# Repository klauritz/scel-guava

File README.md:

# Smart Campus Energy Lab - Team Guava
Current Members: Sawinna Huang, Kenneth Lauritzen, Rammell Transfiguracion

*** 
Welcome to Team Guava's repo!

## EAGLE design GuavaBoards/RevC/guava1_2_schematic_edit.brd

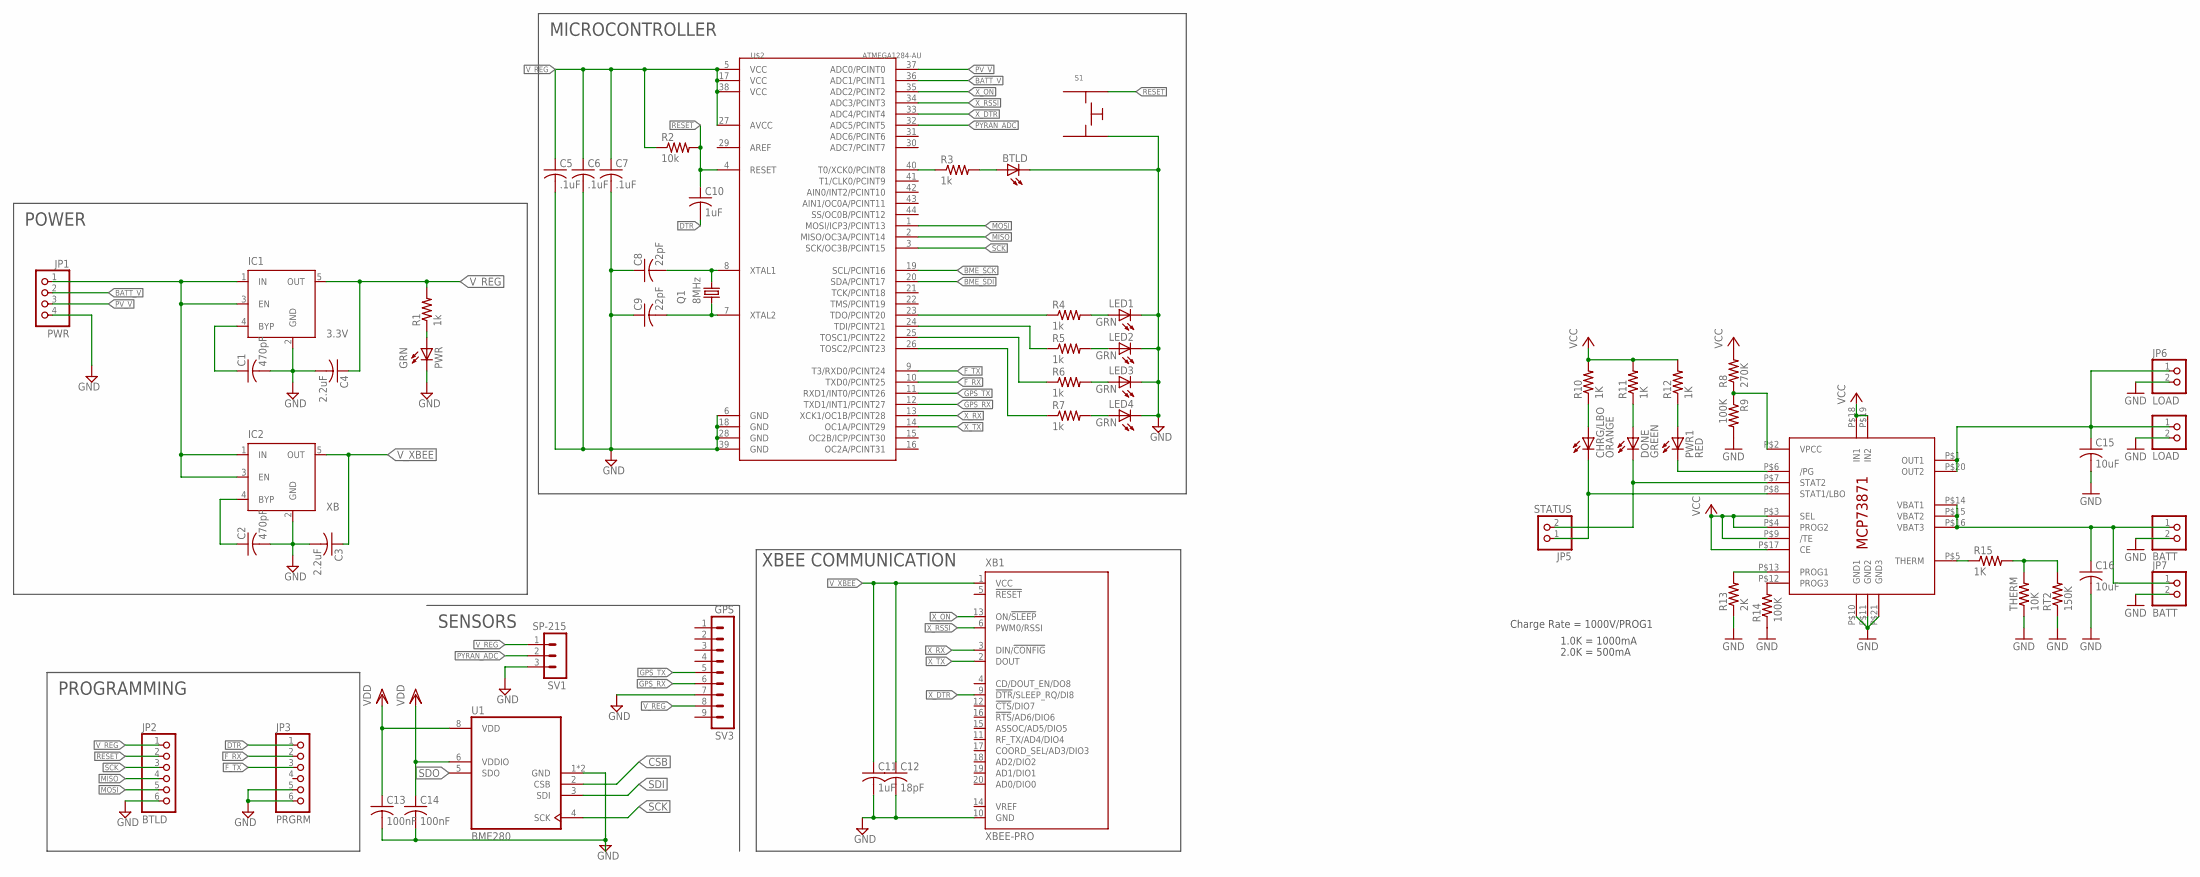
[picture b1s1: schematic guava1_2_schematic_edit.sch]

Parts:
BATT: JST_2PIN-SMT-RA; JST-PH-2-SMT-RA
BTLD: LEDCHIPLED_0805; CHIPLED_0805
C1, C2: 470pF; C0402
C3, C4: 2.2uF; C0603
C5, C6, C7: .1uF; C0603
C8, C9: 22pF; C0402
C10, C11: 1uF; C0805
C12: 18pF; C0805
C13, C14: 100nF; C025-024X044
C15, C16: 10uF; C0805K
CHRG/LBO: ORANGE; CHIP-LED0805
DONE: GREEN; CHIP-LED0805
IC1: 3.3V; SOT23-5
IC2: XB; SOT23-5
IC3: MCP73871; QFN20_4MM
JP1: PWR; 1X04
JP2: BTLD; 1X06
JP3: PRGRM; 1X06
JP5: STATUS; 1X02_OVAL
JP6: LOAD; 1X02_OVAL
JP7: BATT; 1X02_OVAL
LED1, LED2, LED3, LED4: GRN; CHIPLED_0805
LOAD: JST_2PIN-SMT-RA; JST-PH-2-SMT-RA
PWR: GRN; CHIPLED_0805
PWR1: RED; CHIP-LED0805
Q1: 8MHz; HC49UP
R1, R3, R4, R5, R6, R7: 1k; R0603
R2: 10k; R0603
R8: 270K; R0805
R9, R14: 100K; R0805
R10, R11, R12: 1K; R0805
R13: 2K; 0805-THM
R15: 1K; M0805
RT2: 150K; M0805
S1: PUSH_BUTTON_SPSTSMD; COM-12993
SV1: SP-215; MA03-1
SV3: GPS; MA09-1
THERM: 10K; 0805-THM
U1: BME280; PSON65P250X250X100-8N
U$2: ATMEGA1284-AU; 44A
XB1: XBEE-PRO

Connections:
BATT: BATT.1 (2), C16.1, IC3.P$14 (VBAT1), IC3.P$15 (VBAT2), IC3.P$16 (VBAT3), JP7.1
BATT_V: JP1.2, U$2.36 (ADC1/PCINT1)
BME_SCK: U$2.19 (SCL/PCINT16)
BME_SDI: U$2.20 (SDA/PCINT17)
CSB: C13.2, C14.2, U1.1 (GND), U1.2 (CSB), U1.7 (GND)
DTR: C10.2, JP3.1
F_RX: JP3.2, U$2.10 (TXD0/PCINT25)
F_TX: JP3.3, U$2.9 (T3/RXD0/PCINT24)
GND: BATT.2 (1), BTLD.C, C1.2, C2.2, C3.2, C4.2, C5.2, C6.2, C7.2, C8.1, C9.1, C11.2, C12.2, C15.2, C16.2, IC1.2 (GND), IC2.2 (GND), IC3.P$10 (GND1), IC3.P$11 (GND2), IC3.P$21 (GND3), JP1.4, JP2.6, JP3.5, JP3.6, JP6.2, JP7.2, LED1.C, LED2.C, LED3.C, LED4.C, LOAD.2 (1), PWR.C, R9.2, R13.1, R14.1, RT2.1, S1.3, SV1.3, SV3.7, THERM.1, U$2.6 (GND), U$2.18 (GND), U$2.28 (GND), U$2.39 (GND), XB1.10 (GND)
GPS_RX: SV3.6, U$2.12 (TXD1/INT1/PCINT27)
GPS_TX: SV3.5, U$2.11 (RXD1/INT0/PCINT26)
LED1: R4.1, U$2.23 (TDO/PCINT20)
LED2: R5.1, U$2.24 (TDI/PCINT21)
LED3: R6.1, U$2.25 (TOSC1/PCINT22)
LED4: R7.1, U$2.26 (TOSC2/PCINT23)
MISO: JP2.4, U$2.2 (MISO/OC3A/PCINT14)
MOSI: JP2.5, U$2.1 (MOSI/ICP3/PCINT13)
unnamed: C8.2, Q1.2, U$2.8 (XTAL1)
unnamed: C9.2, Q1.1, U$2.7 (XTAL2)
unnamed: BTLD.A, R3.2
unnamed: R3.1, U$2.40 (T0/XCK0/PCINT8)
unnamed: IC3.P$2 (VPCC), R8.1, R9.1
unnamed: C1.1, IC1.4 (BYP)
unnamed: PWR.A, R1.1
unnamed: LED4.A, R7.2
unnamed: LED2.A, R5.2
unnamed: LED3.A, R6.2
unnamed: LED1.A, R4.2
unnamed: IC3.P$6 (/PG), PWR1.C
unnamed: DONE.C, IC3.P$7 (STAT2), JP5.2
unnamed: C2.1, IC2.4 (BYP)
unnamed: CHRG/LBO.C, IC3.P$8 (STAT1/LBO), JP5.1
unnamed: CHRG/LBO.A, R10.1
unnamed: DONE.A, R11.1
unnamed: PWR1.A, R12.1
unnamed: IC3.P$12 (PROG3), R14.2
unnamed: IC3.P$13 (PROG1), R13.2
unnamed: C15.1, IC3.P$1 (OUT1), IC3.P$20 (OUT2), JP6.1, LOAD.1 (2)
unnamed: IC3.P$5 (THERM), R15.1
unnamed: R15.2, RT2.2, THERM.2
PV_V: JP1.3, U$2.37 (ADC0/PCINT0)
PYRAN_ADC: SV1.2, U$2.32 (ADC5/PCINT5)
RESET: C10.1, JP2.2, R2.2, S1.2, U$2.4 (RESET)
SCK: JP2.3, U1.4 (SCK), U$2.3 (SCK/OC3B/PCINT15)
SDI: U1.3 (SDI)
SDO: C14.1, U1.6 (VDDIO)
VCC: IC3.P$3 (SEL), IC3.P$4 (PROG2), IC3.P$9 (/TE), IC3.P$17 (CE), IC3.P$18 (IN1), IC3.P$19 (IN2), R8.2, R10.2, R11.2, R12.2
VDD: C13.1, U1.8 (VDD)
V_LOAD: IC1.1 (IN), IC1.3 (EN), IC2.1 (IN), IC2.3 (EN), JP1.1
V_REG: C4.1, C5.1, C6.1, C7.1, IC1.5 (OUT), JP2.1, R1.2, R2.1, SV1.1, SV3.8, U$2.5 (VCC), U$2.17 (VCC), U$2.27 (AVCC), U$2.38 (VCC)
V_XBEE: C3.1, C11.1, C12.1, IC2.5 (OUT), XB1.1 (VCC)
X_DTR: U$2.33 (ADC4/PCINT4), XB1.9 (!DTR!/SLEEP_RQ/DI8)
X_ON: U$2.35 (ADC2/PCINT2), XB1.13 (ON/!SLEEP)
X_RSSI: U$2.34 (ADC3/PCINT3), XB1.6 (PWM0/RSSI)
X_RX: U$2.13 (XCK1/OC1B/PCINT28), XB1.3 (DIN/!CONFIG)
X_TX: U$2.14 (OC1A/PCINT29), XB1.2 (DOUT)

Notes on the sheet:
XBEE COMMUNICATION
SENSORS
POWER
PROGRAMMING
MICROCONTROLLER
Charge Rate = 1000V/PROG1
1.0K = 1000mA
2.0K = 500mA

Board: 2 copper layers, 60 parts (0 on the bottom side), 53 nets, no tracks yet.

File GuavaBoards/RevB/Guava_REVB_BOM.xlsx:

Column1 | Column2 | Column3 | Column4 | Column5 | Column6 | Column7 | Column8 | Column9 | Column10
Part | Value | Device | Package | Description | MF | MPN | OC_FARNELL | OC_NEWARK
BTLD |  | LEDCHIPLED_0805 | CHIPLED_0805 | LED
C1 | 470pF | C-USC0402 | C0402 | CAPACITOR, American symbol
C2 | 470pF | C-USC0402 | C0402 | CAPACITOR, American symbol
C3 | 2.2uF | C-USC0603 | C0603 | CAPACITOR, American symbol
C4 | 2.2uF | C-USC0603 | C0603 | CAPACITOR, American symbol
C5 | .1uF | C-USC0603 | C0603 | CAPACITOR, American symbol
C6 | .1uF | C-USC0603 | C0603 | CAPACITOR, American symbol
C7 | .1uF | C-USC0603 | C0603 | CAPACITOR, American symbol
C8 | 22pF | C-USC0402 | C0402 | CAPACITOR, American symbol
C9 | 22pF | C-USC0402 | C0402 | CAPACITOR, American symbol
C10 | 1uF | C-USC0805 | C0805 | CAPACITOR, American symbol
C11 | 1uF | C-USC0805 | C0805 | CAPACITOR, American symbol
C12 | 18pF | C-USC0805 | C0805 | CAPACITOR, American symbol
IC1 | 3.3V | MIC5219XX | SOT23-5 | VOLTAGE REGULATOR |  |  | unknown | unknown
IC2 | XB | MIC5219XX | SOT23-5 | VOLTAGE REGULATOR |  |  | unknown | unknown
JP1 | PWR | PINHD-1X4 | 1X04 | PIN HEADER
JP2 | BTLD | PINHD-1X6 | 1X06 | PIN HEADER
JP3 | PRGRM | PINHD-1X6 | 1X06 | PIN HEADER
LED1 | GRN | LEDCHIPLED_0805 | CHIPLED_0805 | LED
LED2 | GRN | LEDCHIPLED_0805 | CHIPLED_0805 | LED
LED3 | GRN | LEDCHIPLED_0805 | CHIPLED_0805 | LED
LED4 | GRN | LEDCHIPLED_0805 | CHIPLED_0805 | LED
PWR | GRN | LEDCHIPLED_0805 | CHIPLED_0805 | LED
Q1 | 8MHz | CRYSTALHC49UP | HC49UP | CRYSTAL |  |  | unknown | unknown
R1 | 1k | R-US_R0603 | R0603 | RESISTOR, American symbol
R2 | 10k | R-US_R0603 | R0603 | RESISTOR, American symbol
R3 | 1k | R-US_R0603 | R0603 | RESISTOR, American symbol
R4 | 1k | R-US_R0603 | R0603 | RESISTOR, American symbol
R5 | 1k | R-US_R0603 | R0603 | RESISTOR, American symbol
R6 | 1k | R-US_R0603 | R0603 | RESISTOR, American symbol
R7 | 1k | R-US_R0603 | R0603 | RESISTOR, American symbol
S1 |  | PUSH_BUTTON_SPSTSMD | COM-12993 | COM-12993 - SMD 12mm square SPST button. This button is great for user input or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
SV1 | SP-215 | MA03-1 | MA03-1 | PIN HEADER |  |  | unknown | unknown
SV2 | BME | MA07-1 | MA07-1 | PIN HEADER |  |  | unknown | unknown
SV3 | GPS | MA09-1 | MA09-1 | PIN HEADER |  |  | unknown | unknown
U1 |  | MEGA1284P-TQFP44SMT-TQFP44 | TQFP44
XB1 | XBEE-PRO | XBEE-PRO | XBEE-PRO | XBee (TM) /XBee-PRO(TM) OEM RF Modules |  | XBP24-AWI-001 | 1337916 | 42M2667

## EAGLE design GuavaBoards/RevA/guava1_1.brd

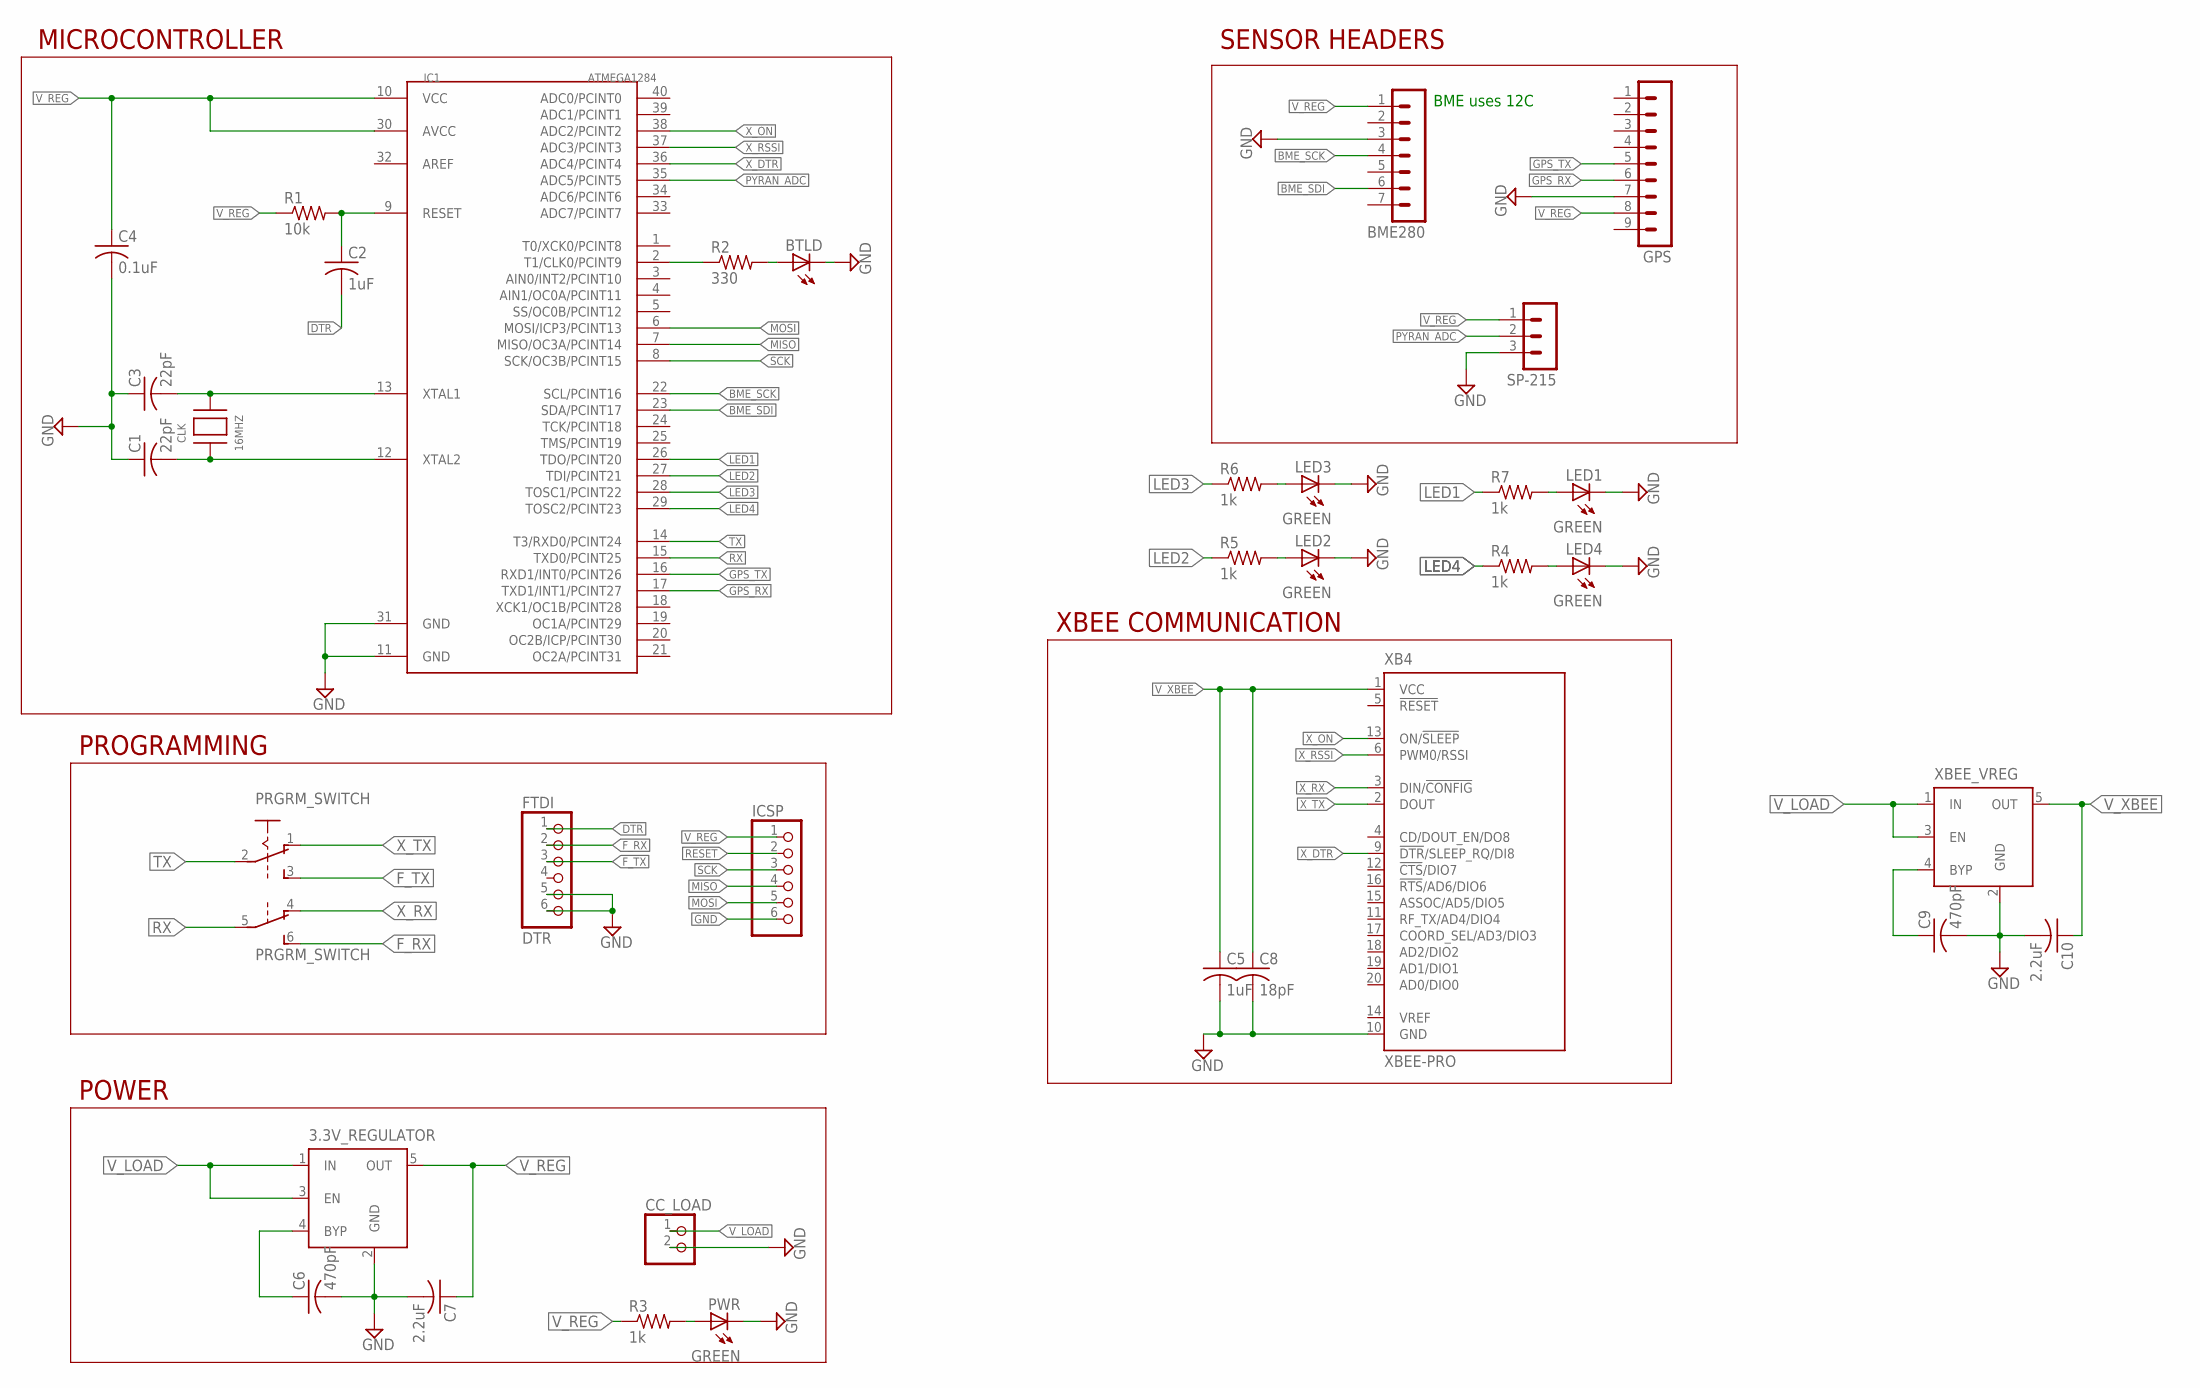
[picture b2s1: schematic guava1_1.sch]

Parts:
3.3V_REGULATOR: MIC5219XX; SOT23-5
BME280: MA07-1
BTLD: LEDCHIPLED_0805; CHIPLED_0805
C1, C3: 22pF; C0805
C2, C5: 1uF; C0805
C4: 0.1uF; C0805
C6, C9: 470pF; C0805
C7, C10: 2.2uF; C0805
C8: 18pF; C0805
CC_LOAD: PINHD-1X2; 1X02
CLK: 16MHZ; NX8045
FTDI: DTR; 1X06
GPS: MA09-1
IC1: ATMEGA1284; DIL40
ICSP: PINHD-1X6; 1X06
LED1, LED2, LED3, LED4: GREEN; CHIPLED_0805
PRGRM_SWITCH: A68-A31
PWR: GREEN; CHIPLED_0805
R1: 10k; R0805
R2: 330; R0805
R3, R4, R5, R6, R7: 1k; R0805
SP-215: MA03-1
XB4: XBEE-PRO
XBEE_VREG: MIC5219XX; SOT23-5

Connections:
BME_SCK: BME280.4, IC1.22 (SCL/PCINT16)
BME_SDI: BME280.6, IC1.23 (SDA/PCINT17)
DTR: C2.2, FTDI.1
F_RX: FTDI.2, PRGRM_SWITCH.6 (S)
F_TX: FTDI.3, PRGRM_SWITCH.3 (S)
GND: 3.3V_REGULATOR.2 (GND), BME280.3, BTLD.C, C1.1, C3.1, C4.2, C5.2, C6.2, C7.2, C8.2, C9.2, C10.2, CC_LOAD.2, FTDI.5, FTDI.6, GPS.7, IC1.11 (GND), IC1.31 (GND), ICSP.6, LED1.C, LED2.C, LED3.C, LED4.C, PWR.C, SP-215.3, XB4.10 (GND), XBEE_VREG.2 (GND)
GPS_RX: GPS.6, IC1.17 (TXD1/INT1/PCINT27)
GPS_TX: GPS.5, IC1.16 (RXD1/INT0/PCINT26)
LED1: IC1.26 (TDO/PCINT20), R7.1
LED2: IC1.27 (TDI/PCINT21), R5.1
LED3: IC1.28 (TOSC1/PCINT22), R6.1
LED4: IC1.29 (TOSC2/PCINT23), R4.1
MISO: IC1.7 (MISO/OC3A/PCINT14), ICSP.4
MOSI: IC1.6 (MOSI/ICP3/PCINT13), ICSP.5
unnamed: C3.2, CLK.P$2, IC1.13 (XTAL1)
unnamed: C1.2, CLK.P$1, IC1.12 (XTAL2)
unnamed: C2.1, IC1.9 (RESET), R1.2
unnamed: IC1.2 (T1/CLK0/PCINT9), R2.1
unnamed: BTLD.A, R2.2
unnamed: 3.3V_REGULATOR.4 (BYP), C6.1
unnamed: PWR.A, R3.2
unnamed: LED4.A, R4.2
unnamed: LED2.A, R5.2
unnamed: LED3.A, R6.2
unnamed: LED1.A, R7.2
unnamed: C9.1, XBEE_VREG.4 (BYP)
PYRAN_ADC: IC1.35 (ADC5/PCINT5), SP-215.2
RESET: ICSP.2
RX: IC1.15 (TXD0/PCINT25), PRGRM_SWITCH.5
SCK: IC1.8 (SCK/OC3B/PCINT15), ICSP.3
TX: IC1.14 (T3/RXD0/PCINT24), PRGRM_SWITCH.2
V_LOAD: 3.3V_REGULATOR.1 (IN), 3.3V_REGULATOR.3 (EN), CC_LOAD.1, XBEE_VREG.1 (IN), XBEE_VREG.3 (EN)
V_REG: 3.3V_REGULATOR.5 (OUT), BME280.1, C4.1, C7.1, GPS.8, IC1.10 (VCC), IC1.30 (AVCC), ICSP.1, R1.1, R3.1, SP-215.1
V_XBEE: C5.1, C8.1, C10.1, XB4.1 (VCC), XBEE_VREG.5 (OUT)
X_DTR: IC1.36 (ADC4/PCINT4), XB4.9 (!DTR!/SLEEP_RQ/DI8)
X_ON: IC1.38 (ADC2/PCINT2), XB4.13 (ON/!SLEEP)
X_RSSI: IC1.37 (ADC3/PCINT3), XB4.6 (PWM0/RSSI)
X_RX: PRGRM_SWITCH.4 (O), XB4.3 (DIN/!CONFIG)
X_TX: PRGRM_SWITCH.1 (O), XB4.2 (DOUT)

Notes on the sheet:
BME uses 12C
XBEE COMMUNICATION
MICROCONTROLLER
PROGRAMMING
SENSOR HEADERS
POWER

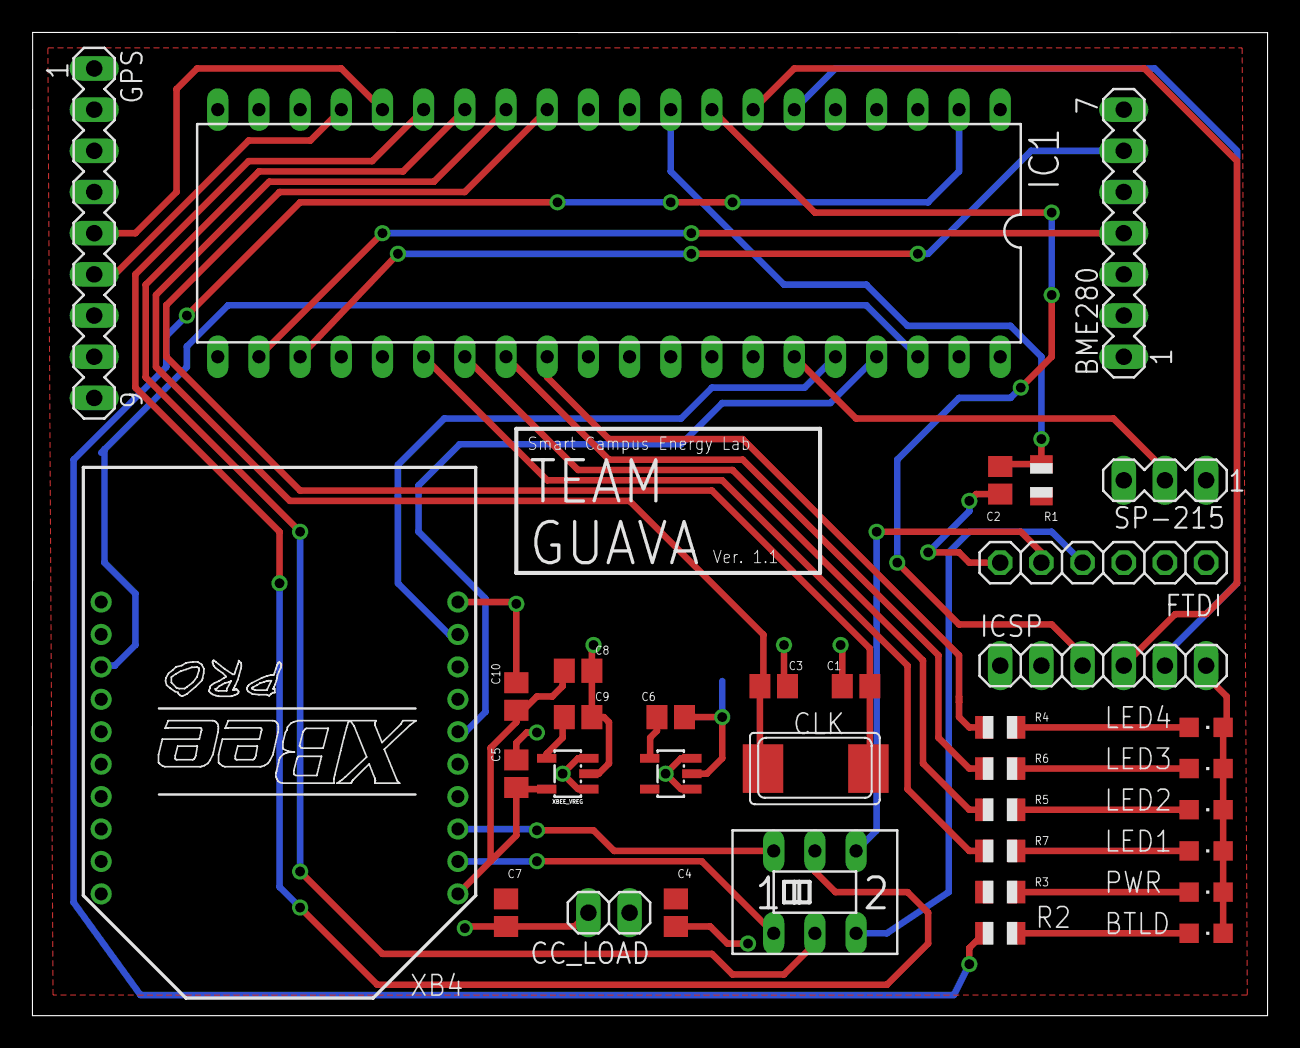
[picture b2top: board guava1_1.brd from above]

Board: 2 copper layers, 76.2 x 60.6 mm, 35 parts (0 on the bottom side), 38 nets.

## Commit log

2018-08-29 Added boards
2018-08-29 added README
2018-08-30 added grber files
2018-08-30 Revised and verified Gerber Files
2018-10-04 //Update: addition with solar charging circuit.
